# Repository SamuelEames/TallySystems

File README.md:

# vMixTally
Tally light system for vMix using Arduino USB MIDI controller, transmitting tally light data to receiver modules on cameras using NRF24L01 radios

## MIDI Map

Notes
* Use midi note value to set colour of LEDs on tally lights

* Channel = 2

Data from vMix
* Preview <Input Number> Note 000-031
* Program <Input Number> Note 100-131
* Streaming

Data from BMD
 * Preview <Input Number>
 * Program <Input Number>
 * AUX 	   <Input Number>

BMD Inputs
1-8
MP 1-2
Col 1-2
FTB

Tally Light Colours
|			| 			| BMD		|			|			|
| --------- | --------- | --------- | --------- | --------- |
|			|			| No Signal	| Program	| Preview	| AUX
| vMix 		| No Signal	| NA		| Yellow	| Blue 		|
|			| Program	| Yellow	| Red		| Green 	|
|			| Preview	| Blue		| Green		| Off 		|

# Resources
BMD-Arduino interface
https://github.com/mathijsk/Arduino-Library-for-ATEM-Switchers 

Insanely cool company
https://www.skaarhoj.com/various/atem-arduino-case-stories/
https://www.skaarhoj.com/support/manual/

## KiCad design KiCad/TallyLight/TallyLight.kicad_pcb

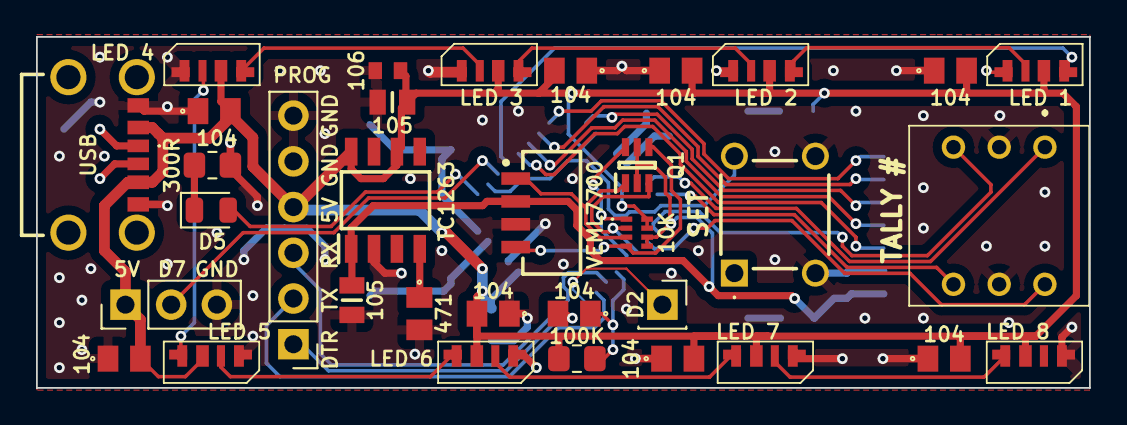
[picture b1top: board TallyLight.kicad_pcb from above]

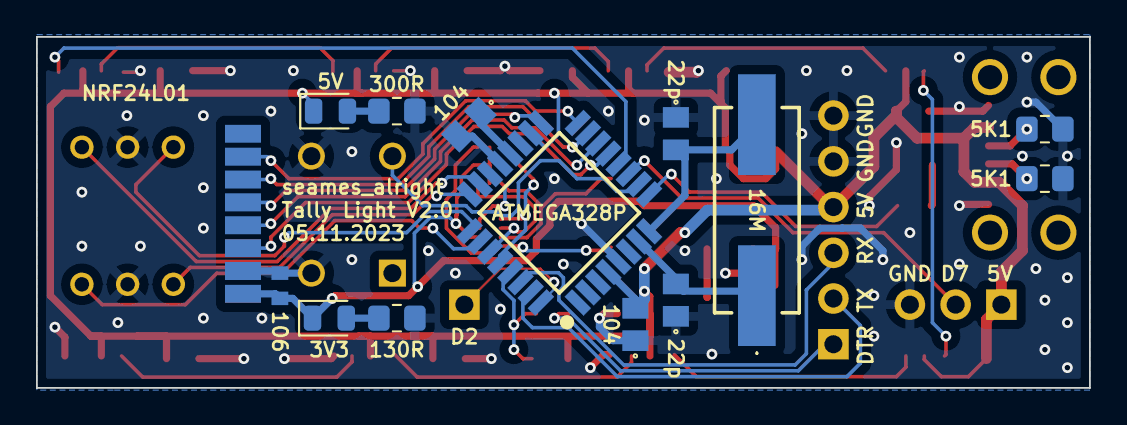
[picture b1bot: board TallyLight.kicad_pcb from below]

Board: 2 copper layers, 58.5 x 19.5 mm, 48 parts (14 on the bottom side), 41 nets.

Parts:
3V3, 5V: LED; LED_0805_2012Metric
16M: 16M; ABLS
ATMEGA328P: ATMEGA328PB-AU; QFP80P900X900X120-32N
C1, C2, C3, C4, C5, C6, C7, C8, C14, C15, C16: 104; C0805
C9, C11: 105; CAPC2012X135N
C10: 471; C0805
C12, C13: 106; CAPC1608X90N
C17, C18: 22p; C0805
D2: Conn_01x01_Pin; PinSocket_1x01_P2.54mm_Vertical
D5: LED; LED_0805_2012Metric
J4: Conn_01x03_Pin; PinHeader_1x03_P2.54mm_Vertical
NRF24L01: NRF24L01; NRF24L01-SMD
PROG: Conn_01x06_Pin; PinHeader_1x06_P2.54mm_Vertical
Q1: BSS138DW-7-F; SOT65P210X110-6N
R1, R2: 5K1; R_0805_2012Metric_Pad1.20x1.40mm_HandSolder
R3: 100K; R_0805_2012Metric_Pad1.20x1.40mm_HandSolder
R4: 130R; R_0805_2012Metric_Pad1.20x1.40mm_HandSolder
R5, R6: 300R; R_0805_2012Metric_Pad1.20x1.40mm_HandSolder
RN1: 10K; YC124JR0710KL
SET: TS02-66-50-BK-260-SCR-D; TS026650BK260SCRD
TALLY #: SD-1210; SD1210
TC1263: TC1263-3.3VOATR; SOIC127P600X175-8N
U1: LED 1; SK6812_SIDE-A
U2: LED 2; SK6812_SIDE-A
U3: LED 3; SK6812_SIDE-A
U4: LED 4; SK6812_SIDE-A
U5: LED 5; SK6812_SIDE-A
U6: LED 6; SK6812_SIDE-A
U7: LED 7; SK6812_SIDE-A
U8: LED 8; SK6812_SIDE-A
USB: USB4125-GF-A-0190; USB4125GFA0190
VEML7700: VEML7700-TT; VEML7700

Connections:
+3V3: 3V3.1 (K), C9.1, C12.1, NRF24L01.2 (VCC), Q1.2 (G2), Q1.5 (G1), RN1.5, RN1.6, TC1263.1 (VOUT), VEML7700.2 (VDD)
+5V: 5V.1 (K), ATMEGA328P.4 (VCC), ATMEGA328P.18 (AVCC), C1.2, C2.2, C3.2, C4.2, C5.2, C6.2, C7.2, C8.2, C11.1, C13.1, C14.2, J4.1, PROG.4, R3.1, RN1.7, RN1.8, TC1263.6 (~SHDN), TC1263.8 (VIN), U1.2 (VDD), U2.2 (VDD), U3.2 (VDD), U4.2 (VDD), U5.2 (VDD), U6.2 (VDD), U7.2 (VDD), U8.2 (VDD), USB.A9 (VBUS_1), USB.B9 (VBUS_2)
/BTN: ATMEGA328P.10 ((OC0A/PTCXY/AIN0)_PD6), SET.2 (NO_2)
/DTR: C15.2, PROG.1
/HEX_1: ATMEGA328P.23 (PC0_(ADC0/PTCY/MISO1)), TALLY #.1
/HEX_2: ATMEGA328P.24 (PC1_(ADC1/PTCY/SCK1)), TALLY #.2
/HEX_4: ATMEGA328P.25 (PC2_(ADC2/PTCY)), TALLY #.4
/HEX_8: ATMEGA328P.26 (PC3_(ADC3/PTCY)), TALLY #.8
/LED: ATMEGA328P.9 ((OC0B/T1/PTCXY)_PD5), D5.2 (A)
/LED_DATA: ATMEGA328P.12 ((ICP1/CLKO/PTCXY)_PB0), U1.1 (DIN)
/LED_DATA_2: ATMEGA328P.11 ((PTCXY/AIN1)_PD7), J4.2
/MISO: ATMEGA328P.16 ((MISO0/RXD1/PTCXY)_PB4), NRF24L01.7 (MISO)
/MOSI: ATMEGA328P.15 ((MOSI0/TXD1/OC2A/PTCXY)_PB3), NRF24L01.6 (MOSI)
/RF_CE: ATMEGA328P.13 ((OC1A/PTCXY)_PB1), NRF24L01.3 (CE)
/RF_CSN: ATMEGA328P.14 ((~SS0/OC1B/PTCXY)_PB2), NRF24L01.4 (CSN)
/RST: ATMEGA328P.29 (PC6_(~RESET)), C15.1, R3.2
/RXI: ATMEGA328P.30 (PD0_(PTCXY/OC3A/RXD0)), PROG.3
/SCK: ATMEGA328P.17 (PB5_(PTCXY/XCK0/SCK0)), NRF24L01.5 (SCK)
/SCL: ATMEGA328P.28 (PC5_(ADC5/PTCY/SCL0)), Q1.6 (D2), RN1.1
/SCL_3V: Q1.1 (S2), RN1.3, VEML7700.1 (SCL)
/SDA: ATMEGA328P.27 (PC4_(ADC4/PTCY/SDA0)), Q1.3 (D1), RN1.2
/SDA_3V: Q1.4 (S1), RN1.4, VEML7700.4 (SDA)
/TXO: ATMEGA328P.31 (PD1_(PTCXY/OC4A/TXD0)), PROG.2
/XTAL1: 16M.1, ATMEGA328P.7 ((XTAL1/TOSC1)_PB6), C17.2
/XTAL2: 16M.2, ATMEGA328P.8 ((XTAL2/TOSC2)_PB7), C18.2
GND: ATMEGA328P.5 (GND_1), ATMEGA328P.21 (GND_2), C1.1, C2.1, C3.1, C4.1, C5.1, C6.1, C7.1, C8.1, C9.2, C10.2, C11.2, C12.2, C13.2, C14.1, C16.2, C17.1, C18.1, J4.3, NRF24L01.1 (GND), PROG.5, PROG.6, R1.2, R2.2, R4.1, R5.1, R6.1, SET.3 (COM_1), SET.4 (COM_2), TALLY #.C1, TALLY #.C2, TC1263.2 (GND), U1.4 (GND), U2.4 (GND), U3.4 (GND), U4.4 (GND), U5.4 (GND), U6.4 (GND), U7.4 (GND), U8.4 (GND), USB.A12 (GND_1), USB.B12 (GND_2), VEML7700.3 (GND)
unnamed: 3V3.2 (A), R4.2
unnamed: 5V.2 (A), R5.2
unnamed: C10.1, TC1263.4 (BYPASS)
unnamed: ATMEGA328P.20 (AREF), C16.1
unnamed: ATMEGA328P.32 (PD2_(PTCXY/INT0/OC3B/OC4B)), D2.1
unnamed: R1.1, USB.A5 (CC1)
unnamed: R2.1, USB.B5 (CC2)
unnamed: D5.1 (K), R6.2
unnamed: U1.3 (DOUT), U2.1 (DIN)
unnamed: U2.3 (DOUT), U3.1 (DIN)
unnamed: U3.3 (DOUT), U4.1 (DIN)
unnamed: U4.3 (DOUT), U5.1 (DIN)
unnamed: U5.3 (DOUT), U6.1 (DIN)
unnamed: U6.3 (DOUT), U7.1 (DIN)
unnamed: U7.3 (DOUT), U8.1 (DIN)

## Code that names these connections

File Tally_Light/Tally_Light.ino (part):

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///////////////////////// IO /////////////////////////

// ///////////////////////// Atmega32u4 
// #define RF_CSN_PIN    18
// #define RF_CE_PIN     19

// #define LED_F_PIN     20
// #define LED_B_PIN     21
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
///////////////////////// Atmega328 
// Radio
#define RF_CE_PIN     9     // 13 - PB1
#define RF_CSN_PIN    10    // 14 - PB2
// SCK  - 17 PB5
// MOSI - 15 PB3
// MISO - 16 PB4
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#define BCD_4         16    // 24 - PC2
#define BCD_8         17    // 23 - PC3

#define BTN_PIN       6

// Outputs
#define PIN_PREV    1
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

//////////////////// RF Variables ////////////////////
RF24 radio(RF_CE_PIN, RF_CSN_PIN);

uint8_t RF_address[] = "TALY0";

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  pinMode(BCD_4, INPUT_PULLUP);
  pinMode(BCD_8, INPUT_PULLUP);

  pinMode(BTN_PIN, INPUT_PULLUP);

  leds[1] = COL_PURPLE;
  FastLED.show();
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  DPRINT(F("MyAddress = "));
  DPRINTLN(MY_TALLY_ID);

  if (!digitalRead(BTN_PIN))
  {
    DPRINTLN("SETUP MODE");
    fill_solid(leds, NUM_LEDS, COL_WHITE);
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
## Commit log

2020-05-11 Added FastLED library
2020-05-16 Reads midi correctly & lights LEDs accordingly
2020-05-16 Fixed some math errors
2020-05-17 Split to Controller & Receiver. Actually works
2020-06-06 Set up variables for BMD integration
2020-06-07 Implemented ATEM commnication
2020-06-07 Created combined vMix ATEM Tally Array
2020-06-07 Transmits tally data array
2020-06-11 Minor updates to Tally Light variables
2021-10-13 Minor Updates
2021-10-13 Overhauling system
2021-10-16 Improved data transmit, tidied up, and broke it
2021-10-19 I UNBROKE IT!
2021-10-20 Tidied code, made it function as a tally light again
2021-10-21 Changed ATEM IP Address
2021-11-30 UDPMulticast basic code for Tally TSL 3.1
2021-11-30 Cleaned up code
2021-11-30 And with that, it's done!
2022-02-01 minor upadtes before major overhaul
2022-02-01 Reformat tally data arrays, and broke radios
2022-02-01 Status lights on controller work but radio comms are still down :(
2022-02-05 Radio decided to work again, but Im not sure why
2022-02-16 Prev &Prog work
2022-02-16 Goes Yellow for PGMI bus
2022-02-16 Tidied up & fixed bugs
2022-10-19 another commit
2022-11-28 started wired TSL tally controller
2023-03-21 Added ATEM exclusive tally base
2023-05-14 Ross firmware update happened and broke how I was pulling tally data. Not changed to grab bus tally from input names in format 'CAM X'
2023-05-14 Added mode flag to select where tally data is sourced from
2023-10-12 started PCB design, implemented BCD switch code
2023-10-28 Tally Light now only uses one pixel LED string
2023-10-28 Updated tally light with dim & timeout functions, added test RF controller
2023-10-28 Minor Updates to schematic
2023-12-05 Made a PCB, added error status on LEDs at power up, probably did many more code changes since the last commit
2024-02-04 updated tally controller to read cam number from any position in the data portion of a tally packet
2024-07-17 Added UDP to Serial tally program
